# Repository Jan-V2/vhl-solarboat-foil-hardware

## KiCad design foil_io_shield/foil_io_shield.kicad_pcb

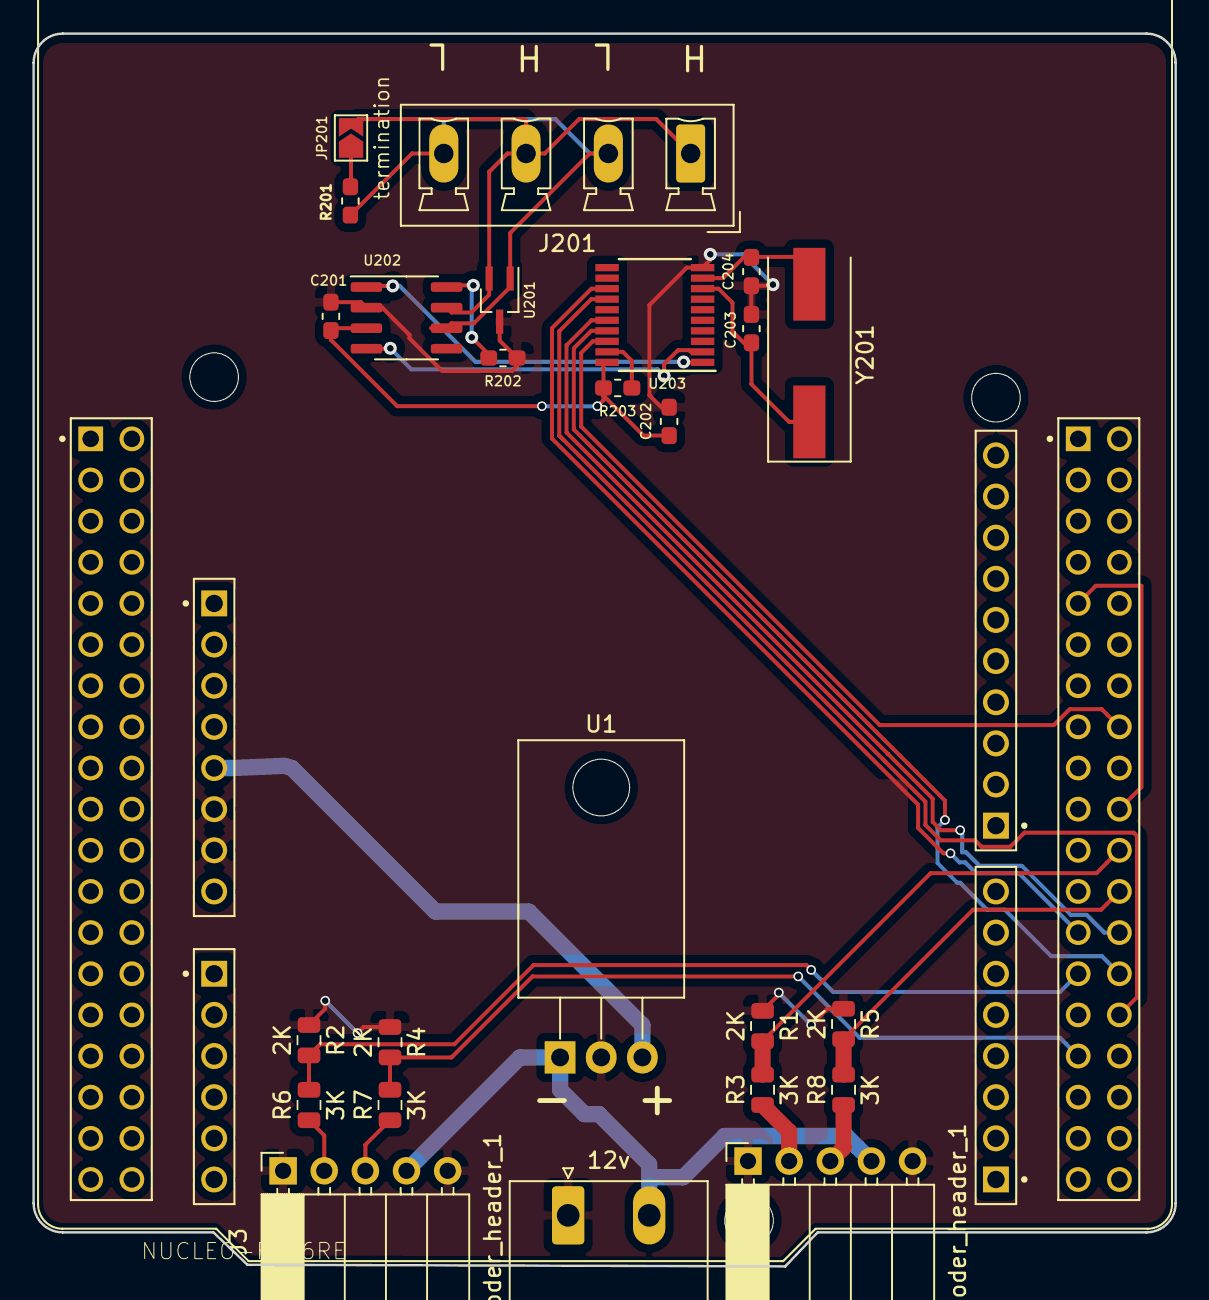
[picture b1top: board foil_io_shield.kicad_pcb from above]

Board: 2 copper layers, 70.5 x 76.1 mm, 26 parts (0 on the bottom side), 26 nets.

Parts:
C201, C202: 100nf; C_0603_1608Metric_Pad1.05x0.95mm_HandSolder
C203, C204: 2pf; C_0603_1608Metric_Pad1.05x0.95mm_HandSolder
J1: 12v; PhoenixContact_MSTBA_2,5_2-G_1x02_P5.00mm_Horizontal
J2, J3: encoder_header_1; PinSocket_1x05_P2.54mm_Horizontal
J201: can; PhoenixContact_MCV_1,5_4-G-5.08_1x04_P5.08mm_Vertical
JP201: termination; SolderJumper-2_P1.3mm_Open_TrianglePad1.0x1.5mm
R1, R2, R4, R5: 2K; R_0805_2012Metric
R3, R6, R7, R8: 3K; R_0805_2012Metric
R201: 120R; R_0603_1608Metric_Pad1.05x0.95mm_HandSolder
R202: 47K; R_0603_1608Metric_Pad1.05x0.95mm_HandSolder
R203: 10K; R_0603_1608Metric_Pad1.05x0.95mm_HandSolder
U1: LM7805_TO220; TO-220-3_Horizontal_TabDown
U2: NUCLEO-F446RE; MODULE_NUCLEO-F446RE
U201: PESD5V0L2UU_esd_diode; SOT-323_SC-70_Handsoldering
U202: MCP2551-I-SN; SOIC-8_3.9x4.9mm_P1.27mm
U203: MCP2515-xST; TSSOP-20_4.4x6.5mm_P0.65mm
Y201: Crystal; Crystal_SMD_HC49-SD

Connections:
+5V: C201.1, C202.1, R203.2, U1.3, U2.CN6_5, U202.3, U203.20
+12V: J1.2, J2.4, J3.4, U1.1
/CAN_CS: U2.CN10_16, U203.18
/CAN_INTR: U2.CN10_25, U203.13
/SPI2_CLK: U2.CN10_30, U203.14
/SPI2_MISO: U2.CN10_28, U203.17
/SPI2_MOSI: U2.CN10_26, U203.16
/Sheet607FE928/can_h: J201.1, J201.3, JP201.2, U201.2, U202.7
/Sheet607FE928/can_l: J201.2, J201.4, R201.2, U201.1, U202.6
/Sheet607FE928/can_rx: U202.4, U203.2
/Sheet607FE928/can_tx: U202.1, U203.1
/enc_1_A: R5.2, R8.2, U2.CN10_24
/enc_1_B: R1.2, R3.2, U2.CN10_22
/enc_2_A: R4.2, R7.2, U2.CN10_31
/enc_2_B: R2.2, R6.2, U2.CN10_27
GND: C201.2, C202.2, C203.1, C204.1, J1.1, J2.1, J2.5, J3.1, J3.5, R1.1, R2.1, R4.1, R5.1, R202.1, U1.2, U2.CN6_6, U2.CN6_7, U201.3, U202.2, U203.10
unnamed: C203.2, U203.8, Y201.1
unnamed: C204.2, U203.9, Y201.2
unnamed: J2.2, R3.1
unnamed: J2.3, R8.1
unnamed: J3.2, R6.1
unnamed: J3.3, R7.1
unnamed: JP201.1, R201.1
unnamed: R202.2, U202.8
unnamed: R203.1, U203.19
unnamed: U2.CN10_9, U2.CN10_20

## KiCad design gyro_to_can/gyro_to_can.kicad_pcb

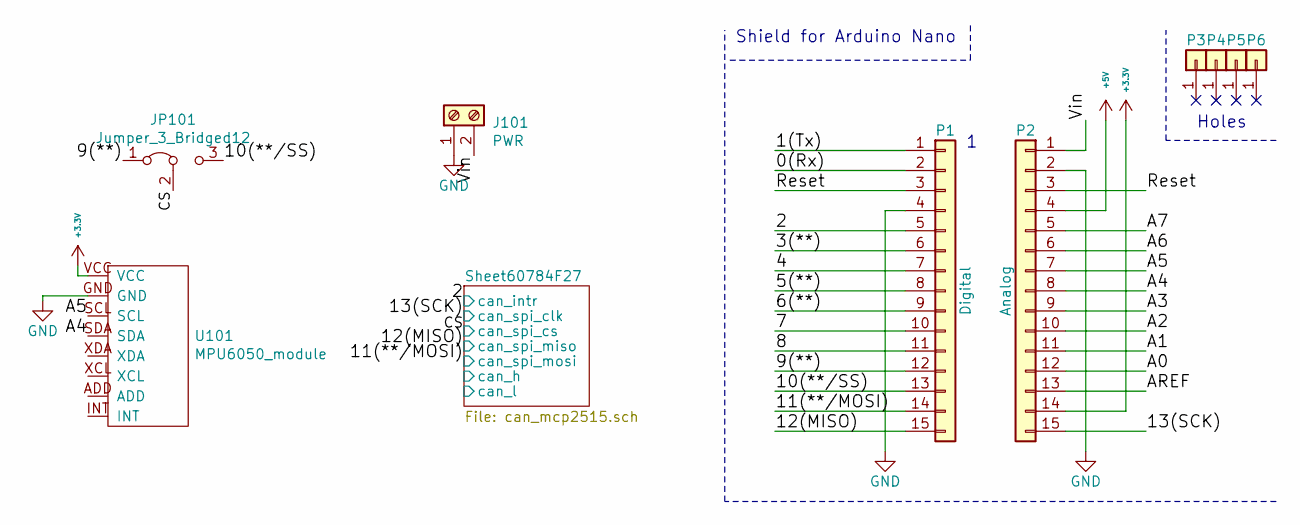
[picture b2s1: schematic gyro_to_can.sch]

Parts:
J101: PWR; PhoenixContact_MCV_1,5_2-G-5.08_1x02_P5.08mm_Vertical
JP101: Jumper_3_Bridged12; SolderJumper-3_P1.3mm_Bridged2Bar12_Pad1.0x1.5mm
P1: Digital; Socket_Strip_Arduino_1x15
P2: Analog; Socket_Strip_Arduino_1x15
P3, P4, P5, P6: CONN_01X01; 1pin_Nano
U101: MPU6050_module; MCP6050_module

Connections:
+3V3: P2.14, U101.VCC
+5V: P2.4; also elsewhere on the board
/0(Rx): P1.2
/1(Tx): P1.1
/2: P1.5; also elsewhere on the board
/3(**): P1.6
/4: P1.7
/5(**): P1.8
/6(**): P1.9
/7: P1.10
/8: P1.11
/9(**): JP101.1 (A), P1.12; also elsewhere on the board
/10(**/SS): JP101.3 (B), P1.13; also elsewhere on the board
/11(**/MOSI): P1.14; also elsewhere on the board
/12(MISO): P1.15; also elsewhere on the board
/13(SCK): P2.15; also elsewhere on the board
/A0: P2.12
/A1: P2.11
/A2: P2.10
/A3: P2.9
/A4: P2.8, U101.SDA
/A5: P2.7, U101.SCL
/A6: P2.6
/A7: P2.5
/AREF: P2.13
/Reset: P1.3, P2.3
/Vin: J101.2, P2.1
GND: J101.1, P1.4, P2.2, U101.GND; also elsewhere on the board

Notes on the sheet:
Holes
Shield for Arduino Nano

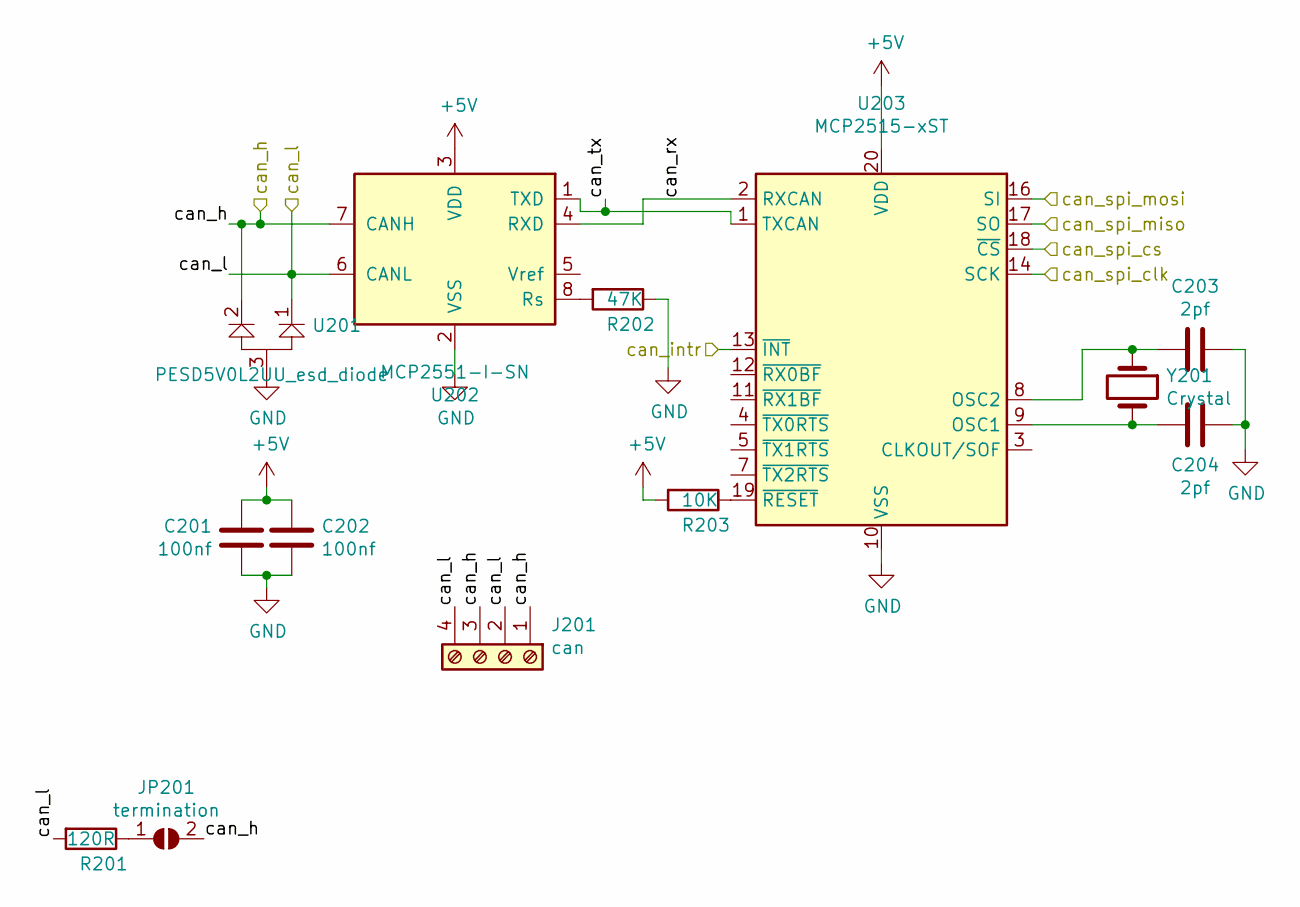
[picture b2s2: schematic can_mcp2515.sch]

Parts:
C201, C202: 100nf; C_0603_1608Metric_Pad1.05x0.95mm_HandSolder
C203, C204: 2pf; C_0603_1608Metric_Pad1.05x0.95mm_HandSolder
J201: can; PhoenixContact_MCV_1,5_4-G-5.08_1x04_P5.08mm_Vertical
JP201: termination; SolderJumper-2_P1.3mm_Open_TrianglePad1.0x1.5mm
R201: 120R; R_0603_1608Metric_Pad1.05x0.95mm_HandSolder
R202: 47K; R_0603_1608Metric_Pad1.05x0.95mm_HandSolder
R203: 10K; R_0603_1608Metric_Pad1.05x0.95mm_HandSolder
U201: PESD5V0L2UU_esd_diode; SOT-323_SC-70_Handsoldering
U202: MCP2551-I-SN; SOIC-8_3.9x4.9mm_P1.27mm
U203: MCP2515-xST; TSSOP-20_4.4x6.5mm_P0.65mm
Y201: Crystal; Crystal_SMD_HC49-SD

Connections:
+5V: C201.1, C202.1, R203.2, U202.3 (VDD), U203.20 (VDD); also elsewhere on the board
/2: U203.13 (~INT); also elsewhere on the board
/11(**/MOSI): U203.16 (SI); also elsewhere on the board
/12(MISO): U203.17 (SO); also elsewhere on the board
/13(SCK): U203.14 (SCK); also elsewhere on the board
/CS: U203.18 (~CS); also elsewhere on the board
/Sheet60784F27/can_h: J201.1, J201.3, JP201.2 (B), U201.2, U202.7 (CANH); also elsewhere on the board
/Sheet60784F27/can_l: J201.2, J201.4, R201.2, U201.1, U202.6 (CANL)
/Sheet60784F27/can_rx: U202.4 (RXD), U203.2 (RXCAN)
/Sheet60784F27/can_tx: U202.1 (TXD), U203.1 (TXCAN)
GND: C201.2, C202.2, C203.1, C204.1, R202.1, U201.3, U202.2 (VSS), U203.10 (VSS); also elsewhere on the board
unnamed: C203.2, U203.8 (OSC2), Y201.1
unnamed: C204.2, U203.9 (OSC1), Y201.2
unnamed 35: JP201.1 (A), R201.1; also elsewhere on the board
unnamed: R202.2, U202.8 (Rs)
unnamed: R203.1, U203.19 (~RESET)

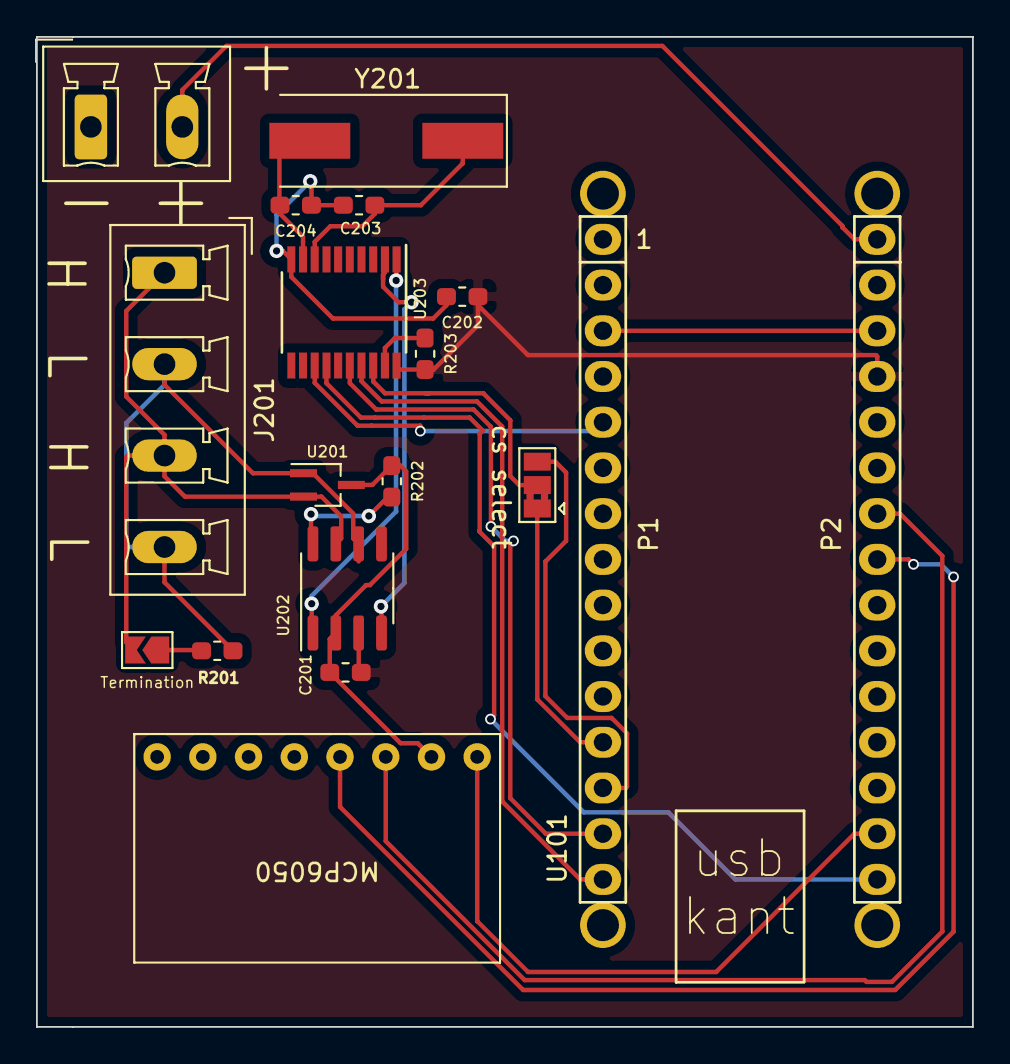
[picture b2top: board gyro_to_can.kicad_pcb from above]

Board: 2 copper layers, 52.0 x 55.0 mm, 22 parts (0 on the bottom side), 23 nets.

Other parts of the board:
Termination: termination; SolderJumper-2_P1.3mm_Open_TrianglePad1.0x1.5mm
cs select: Jumper_3_Bridged12; SolderJumper-3_P1.3mm_Bridged2Bar12_Pad1.0x1.5mm

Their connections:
/9(**): cs select.1; also elsewhere on the board
/10(**/SS): cs select.3; also elsewhere on the board
/CS: cs select.2; also elsewhere on the board
/Sheet60784F27/can_h: Termination.2; also elsewhere on the board
unnamed 35: Termination.1; also elsewhere on the board

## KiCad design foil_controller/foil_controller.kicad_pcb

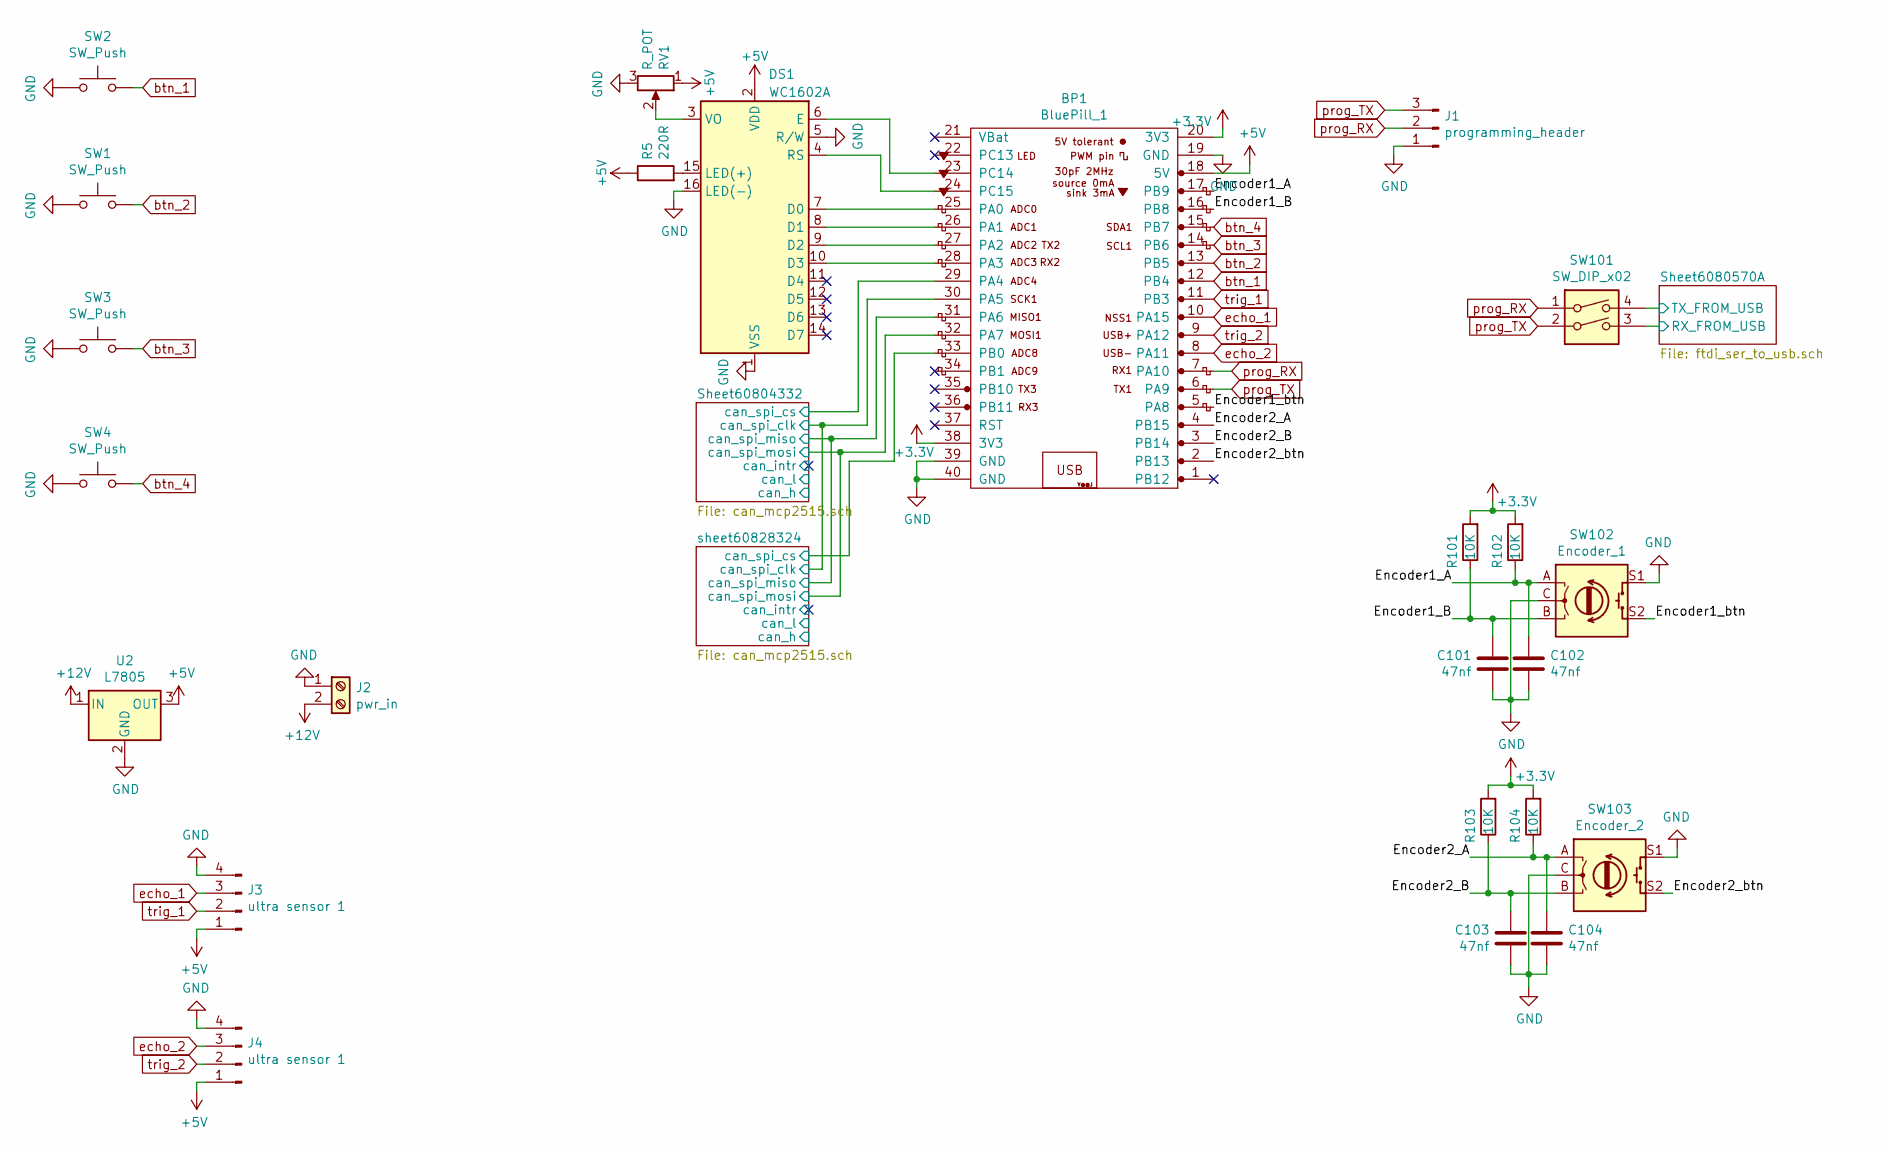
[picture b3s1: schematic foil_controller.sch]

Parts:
BP1: BluePill_1; YAAJ_BluePill
C101, C102, C103, C104: 47nf; C_0603_1608Metric_Pad1.05x0.95mm_HandSolder
DS1: WC1602A; WINSTAR-WH1604A
J1: programming_header; PinSocket_1x03_P2.54mm_Vertical
J2: pwr_in; TerminalBlock_bornier-2_P5.08mm
J3, J4: ultra sensor 1; Molex_SL_171971-0004_1x04_P2.54mm_Vertical
R5: 220R; R_Axial_DIN0207_L6.3mm_D2.5mm_P7.62mm_Horizontal
R101, R102, R103, R104: 10K; R_0603_1608Metric_Pad1.05x0.95mm_HandSolder
RV1: R_POT; multi_turn_trimmers_blue
SW1, SW2, SW3, SW4: SW_Push; SW_PUSH-12mm
SW101: SW_DIP_x02; SW_DIP_SPSTx02_Slide_6.7x6.64mm_W7.62mm_P2.54mm_LowProfile
SW102: Encoder_1; RotaryEncoder_Alps_EC11E-Switch_Vertical_H20mm_CircularMoun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
SW103: Encoder_2; RotaryEncoder_Alps_EC11E-Switch_Vertical_H20mm_CircularMoun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
U2: L7805; TO-220-3_Horizontal_TabDown

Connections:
+3V3: BP1.20 (3V3), BP1.38 (3V3), R101.2, R102.2, R103.2, R104.2
+5V: BP1.18 (5V), DS1.2 (VDD), J3.1, J4.1, R5.1, RV1.1, U2.3 (OUT); also elsewhere on the board
+12V: J2.2, U2.1 (IN)
/Encoder1_A: BP1.17 (PB9), C102.1, R102.1, SW102.A
/Encoder1_B: BP1.16 (PB8), C101.1, R101.1, SW102.B
/Encoder1_btn: BP1.5 (PA8), SW102.S2
/Encoder2_A: BP1.4 (PB15), C104.1, R104.1, SW103.A
/Encoder2_B: BP1.3 (PB14), C103.1, R103.1, SW103.B
/Encoder2_btn: BP1.2 (PB13), SW103.S2
/Sheet6080570A/RX_FROM_USB: SW101.3; also elsewhere on the board
/Sheet6080570A/TX_FROM_USB: SW101.4; also elsewhere on the board
/Sheet60804332/can_spi_clk: BP1.30 (PA5); also elsewhere on the board
/Sheet60804332/can_spi_cs: BP1.29 (PA4); also elsewhere on the board
/Sheet60804332/can_spi_miso: BP1.31 (PA6); also elsewhere on the board
/Sheet60804332/can_spi_mosi: BP1.32 (PA7); also elsewhere on the board
/sheet60828324/can_spi_cs: BP1.33 (PB0); also elsewhere on the board
GND: BP1.19 (GND), BP1.39 (GND), BP1.40 (GND), C101.2, C102.2, C103.2, C104.2, DS1.1 (VSS), DS1.5 (R/W), DS1.16 (LED(-)), J1.1, J2.1, J3.4, J4.4, RV1.3, SW1.1, SW2.1, SW3.1, SW4.1, SW102.C, SW102.S1, SW103.C, SW103.S1, U2.2 (GND); also elsewhere on the board
unnamed: BP1.23 (PC14), DS1.6 (E)
unnamed: BP1.24 (PC15), DS1.4 (RS)
unnamed: BP1.25 (PA0), DS1.7 (D0)
unnamed: BP1.26 (PA1), DS1.8 (D1)
unnamed: BP1.27 (PA2), DS1.9 (D2)
unnamed: BP1.28 (PA3), DS1.10 (D3)
unnamed: DS1.3 (VO), RV1.2
unnamed: DS1.15 (LED(+)), R5.2
btn_1: BP1.12 (PB4), SW2.2
btn_2: BP1.13 (PB5), SW1.2
btn_3: BP1.14 (PB6), SW3.2
btn_4: BP1.15 (PB7), SW4.2
echo_1: BP1.10 (PA15), J3.3
echo_2: BP1.8 (PA11), J4.3
prog_RX: BP1.7 (PA10), J1.2, SW101.1
prog_TX: BP1.6 (PA9), J1.3, SW101.2
trig_1: BP1.11 (PB3), J3.2
trig_2: BP1.9 (PA12), J4.2

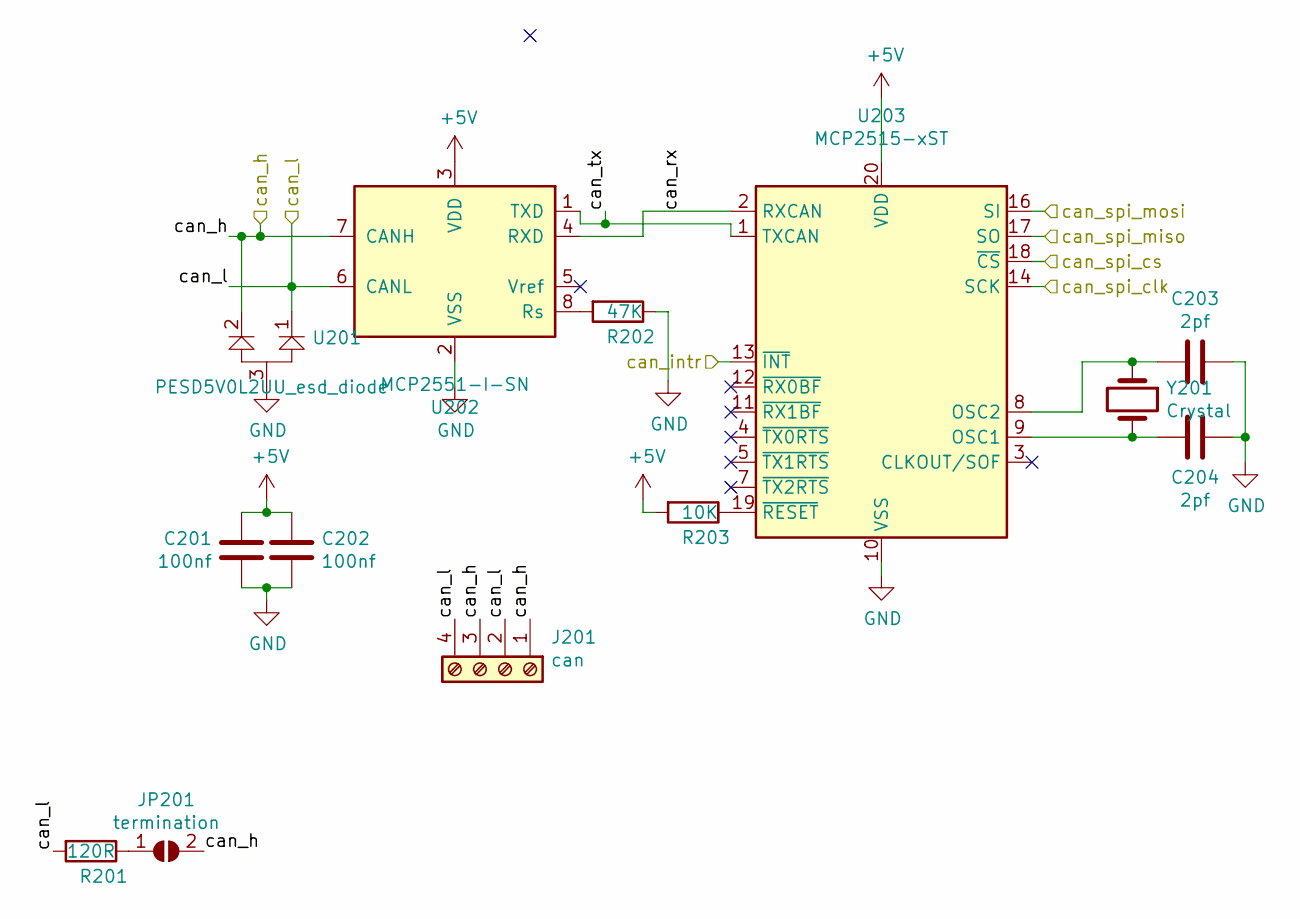
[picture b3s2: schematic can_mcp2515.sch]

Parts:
C201, C202: 100nf; C_0603_1608Metric_Pad1.05x0.95mm_HandSolder
C203, C204: 2pf; C_0603_1608Metric_Pad1.05x0.95mm_HandSolder
J201: can; PhoenixContact_MCV_1,5_4-G-5.08_1x04_P5.08mm_Vertical
JP201: termination; SolderJumper-2_P1.3mm_Open_TrianglePad1.0x1.5mm
R201: 120R; R_0603_1608Metric_Pad1.05x0.95mm_HandSolder
R202: 47K; R_0603_1608Metric_Pad1.05x0.95mm_HandSolder
R203: 10K; R_0603_1608Metric_Pad1.05x0.95mm_HandSolder
U201: PESD5V0L2UU_esd_diode; SOT-323_SC-70_Handsoldering
U202: MCP2551-I-SN; SOIC-8_3.9x4.9mm_P1.27mm
U203: MCP2515-xST; TSSOP-20_4.4x6.5mm_P0.65mm
Y201: Crystal; Crystal_SMD_HC49-SD

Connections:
+5V: C201.1, C202.1, R203.2, U202.3 (VDD), U203.20 (VDD); also elsewhere on the board
/Sheet60804332/can_h: J201.1, J201.3, JP201.2 (B), U201.2, U202.7 (CANH)
/Sheet60804332/can_intr: U203.13 (~INT)
/Sheet60804332/can_l: J201.2, J201.4, R201.2, U201.1, U202.6 (CANL)
/Sheet60804332/can_rx: U202.4 (RXD), U203.2 (RXCAN)
/Sheet60804332/can_spi_clk: U203.14 (SCK); also elsewhere on the board
/Sheet60804332/can_spi_cs: U203.18 (~CS); also elsewhere on the board
/Sheet60804332/can_spi_miso: U203.17 (SO); also elsewhere on the board
/Sheet60804332/can_spi_mosi: U203.16 (SI); also elsewhere on the board
/Sheet60804332/can_tx: U202.1 (TXD), U203.1 (TXCAN)
GND: C201.2, C202.2, C203.1, C204.1, R202.1, U201.3, U202.2 (VSS), U203.10 (VSS); also elsewhere on the board
unnamed: C203.2, U203.8 (OSC2), Y201.1
unnamed: C204.2, U203.9 (OSC1), Y201.2
unnamed: JP201.1 (A), R201.1
unnamed: R202.2, U202.8 (Rs)
unnamed: R203.1, U203.19 (~RESET)

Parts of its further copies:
C401, C402: 100nf; C_0603_1608Metric_Pad1.05x0.95mm_HandSolder
C403, C404: 2pf; C_0603_1608Metric_Pad1.05x0.95mm_HandSolder
J401: can; PhoenixContact_MCV_1,5_4-G-5.08_1x04_P5.08mm_Vertical
JP401: termination; SolderJumper-2_P1.3mm_Open_TrianglePad1.0x1.5mm
R401: 120R; R_0603_1608Metric_Pad1.05x0.95mm_HandSolder
R402: 47K; R_0603_1608Metric_Pad1.05x0.95mm_HandSolder
R403: 10K; R_0603_1608Metric_Pad1.05x0.95mm_HandSolder
U401: PESD5V0L2UU_esd_diode; SOT-323_SC-70_Handsoldering
U402: MCP2551-I-SN; SOIC-8_3.9x4.9mm_P1.27mm
U403: MCP2515-xST; TSSOP-20_4.4x6.5mm_P0.65mm
Y401: Crystal; Crystal_SMD_HC49-SD

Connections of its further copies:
+5V: C401.1, C402.1, R403.2, U402.3 (VDD), U403.20 (VDD); also elsewhere on the board
/Sheet60804332/can_spi_clk: U403.14 (SCK); also elsewhere on the board
/Sheet60804332/can_spi_miso: U403.17 (SO); also elsewhere on the board
/Sheet60804332/can_spi_mosi: U403.16 (SI); also elsewhere on the board
/sheet60828324/can_h: J401.1, J401.3, JP401.2 (B), U401.2, U402.7 (CANH)
/sheet60828324/can_intr: U403.13 (~INT)
/sheet60828324/can_l: J401.2, J401.4, R401.2, U401.1, U402.6 (CANL)
/sheet60828324/can_rx: U402.4 (RXD), U403.2 (RXCAN)
/sheet60828324/can_spi_cs: U403.18 (~CS); also elsewhere on the board
/sheet60828324/can_tx: U402.1 (TXD), U403.1 (TXCAN)
GND: C401.2, C402.2, C403.1, C404.1, R402.1, U401.3, U402.2 (VSS), U403.10 (VSS); also elsewhere on the board
unnamed: C403.2, U403.8 (OSC2), Y401.1
unnamed: C404.2, U403.9 (OSC1), Y401.2
unnamed: JP401.1 (A), R401.1
unnamed: R402.2, U402.8 (Rs)
unnamed: R403.1, U403.19 (~RESET)

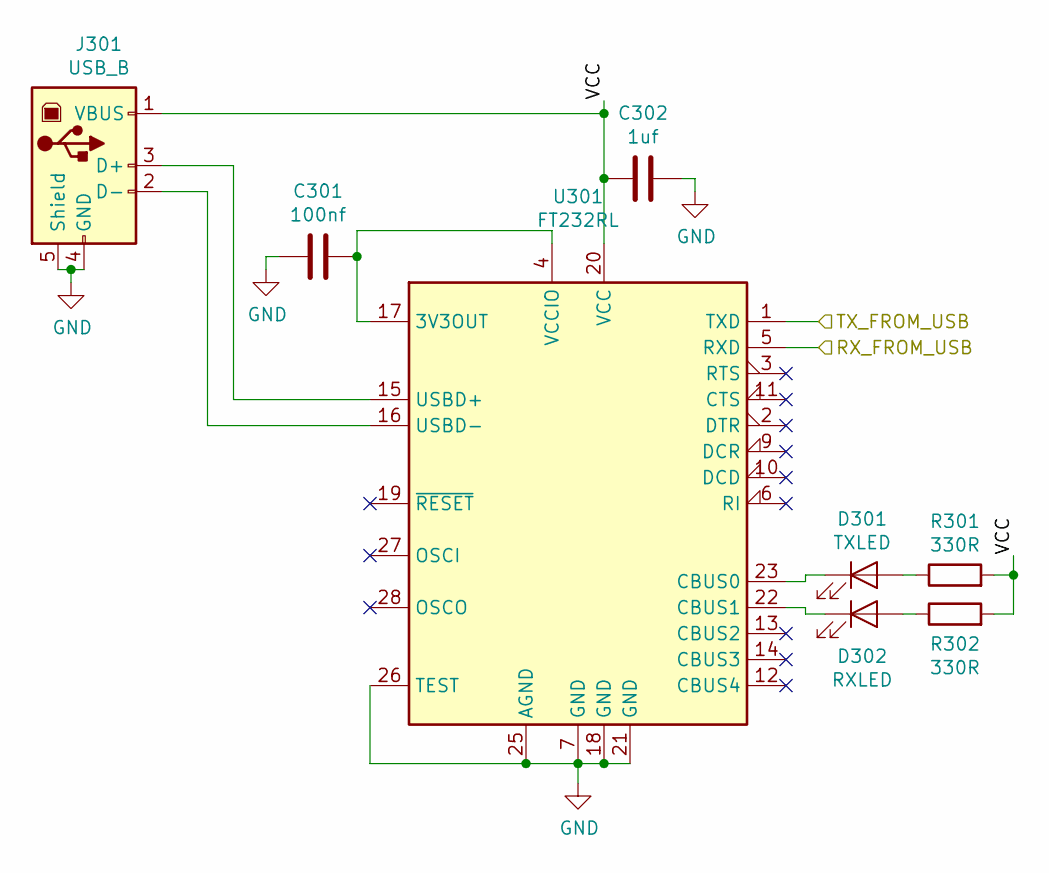
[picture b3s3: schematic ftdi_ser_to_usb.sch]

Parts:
C301: 100nf; C_0603_1608Metric
C302: 1uf; C_0603_1608Metric
D301: TXLED; LED_0805_2012Metric
D302: RXLED; LED_0805_2012Metric
J301: USB_B; USB_B_TE_5787834_Vertical
R301, R302: 330R; R_0603_1608Metric
U301: FT232RL; SSOP-28_5.3x10.2mm_P0.65mm

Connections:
/Sheet6080570A/RX_FROM_USB: U301.5 (RXD); also elsewhere on the board
/Sheet6080570A/TX_FROM_USB: U301.1 (TXD); also elsewhere on the board
/Sheet6080570A/VCC: C302.2, J301.1 (VBUS), R301.2, R302.2, U301.20 (VCC)
GND: C301.2, C302.1, J301.4 (GND), J301.5 (Shield), U301.7 (GND), U301.18 (GND), U301.21 (GND), U301.25 (AGND), U301.26 (TEST); also elsewhere on the board
unnamed: C301.1, U301.4 (VCCIO), U301.17 (3V3OUT)
unnamed: D301.1 (K), U301.23 (CBUS0)
unnamed: D301.2 (A), R301.1
unnamed: D302.1 (K), U301.22 (CBUS1)
unnamed: D302.2 (A), R302.1
unnamed: J301.2 (D-), U301.16 (USBD-)
unnamed: J301.3 (D+), U301.15 (USBD+)

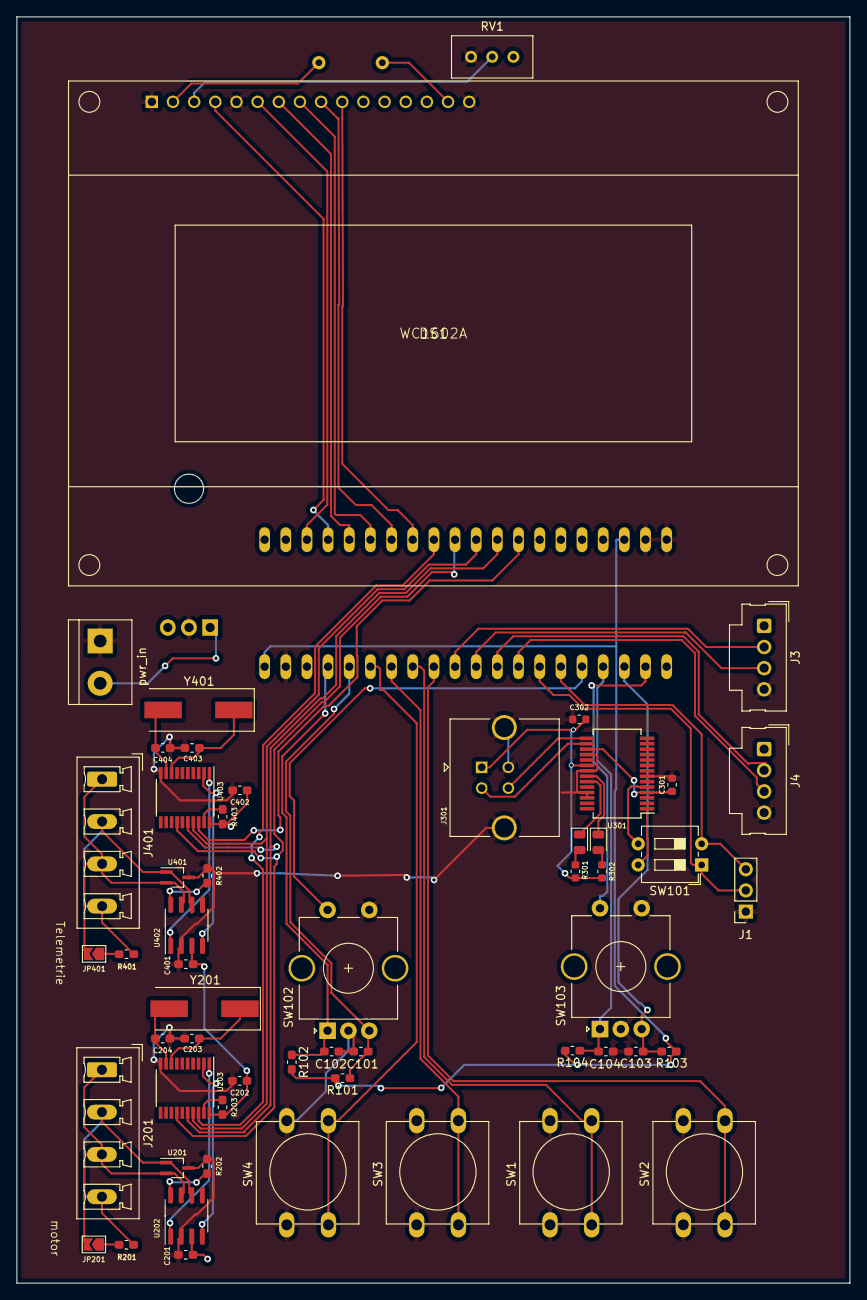
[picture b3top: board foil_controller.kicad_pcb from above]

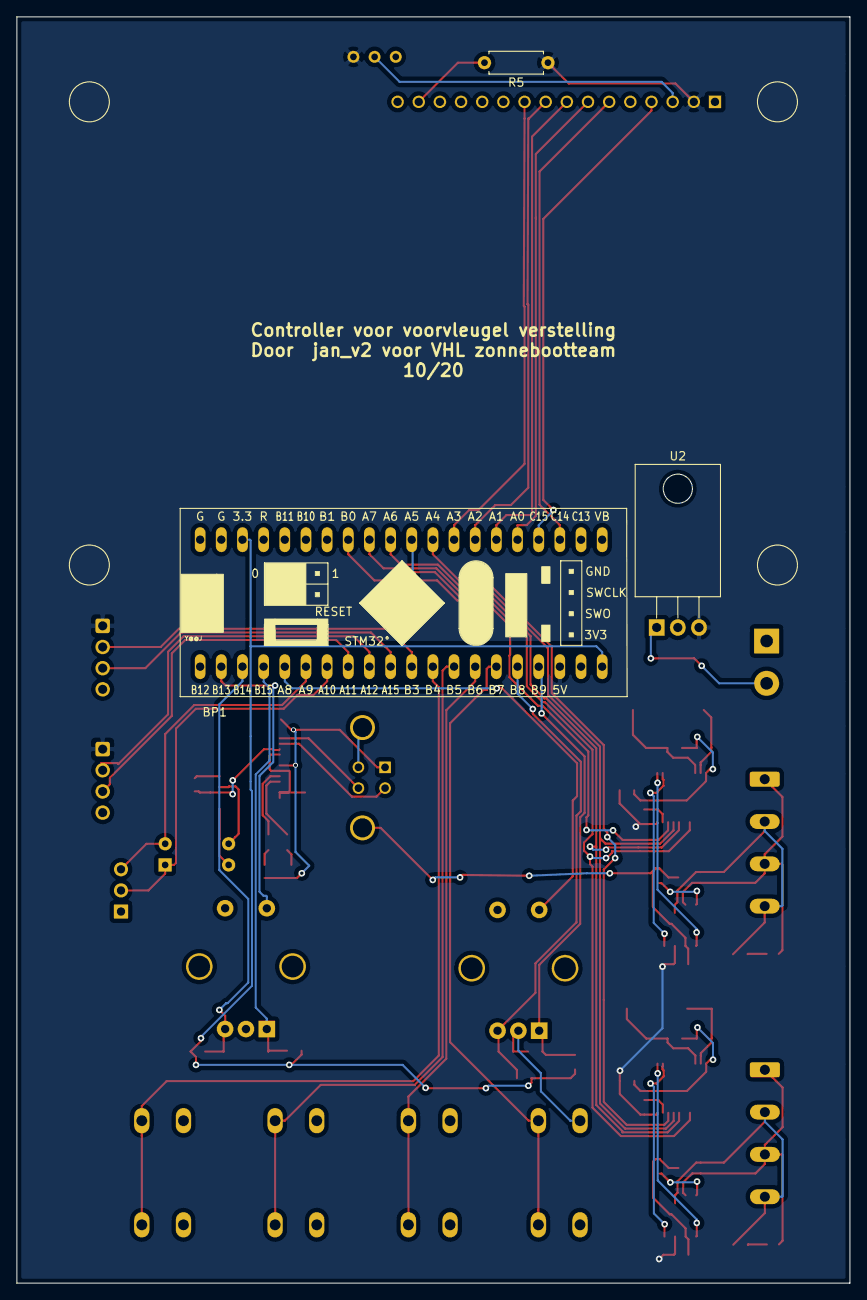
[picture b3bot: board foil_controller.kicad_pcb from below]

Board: 2 copper layers, 100.0 x 152.0 mm, 58 parts (3 on the bottom side), 61 nets.

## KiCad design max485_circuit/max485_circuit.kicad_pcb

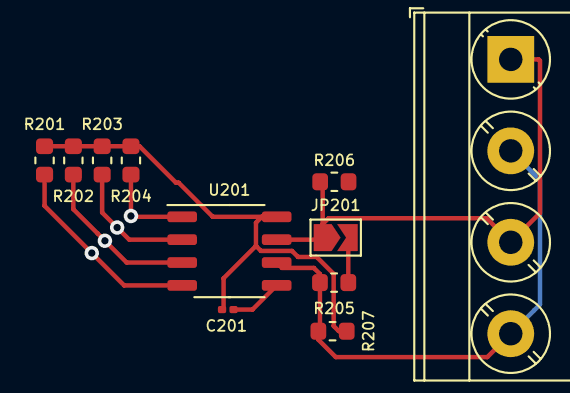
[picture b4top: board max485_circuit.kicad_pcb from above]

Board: 2 copper layers, 11 parts (0 on the bottom side), 9 nets.

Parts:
C201: 100nf; C_0201_0603Metric
J201: RS485 out; TerminalBlock_Phoenix_MKDS-3-4-5.08_1x04_P5.08mm_Horizontal
JP201: bus terminator; SolderJumper-2_P1.3mm_Open_TrianglePad1.0x1.5mm
R201, R202, R203, R204: 10K; R_0603_1608Metric
R205: 120R; R_0603_1608Metric
R206, R207: 20K; R_0603_1608Metric
U201: MAX485E; SOP-8_3.9x4.9mm_P1.27mm

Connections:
+5V: C201.1, R201.1, R202.1, R203.1, R204.1, R207.2, U201.8
/testestestest/Driver_enable: R202.2, U201.3
/testestestest/Driver_in: R201.2, U201.4
/testestestest/Reciever_enable: R203.2, U201.2
/testestestest/Reciever_out: R204.2, U201.1
GND: C201.2, R206.1, U201.5
unnamed: J201.1, J201.3, JP201.1, R206.2, U201.7
unnamed: J201.2, J201.4, R205.2, R207.1, U201.6
unnamed: JP201.2, R205.1

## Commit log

2021-04-13 intitial
2021-04-23 controller v2 voor testvaart 1 mei
2021-05-29 initial
